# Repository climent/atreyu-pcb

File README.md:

# atreyu-pcb
## Intro 
This project is the evolution of the [Atreyu Keyboard](http://github.com/climent/atreyu) project, an ergonomic keyboard that was handwired only.

I aimed to increase the appeal of this board by designing a PCB for it, and through the next months learned how to design one.

The first release of the keyboard (v0.1) is ready, and looks like this:

## Want to collaborate?

You can execute

```git clone --recurse-submodules https://github.com/climent/atryeu-pcb.git```

and send me a pull request.

have fun!

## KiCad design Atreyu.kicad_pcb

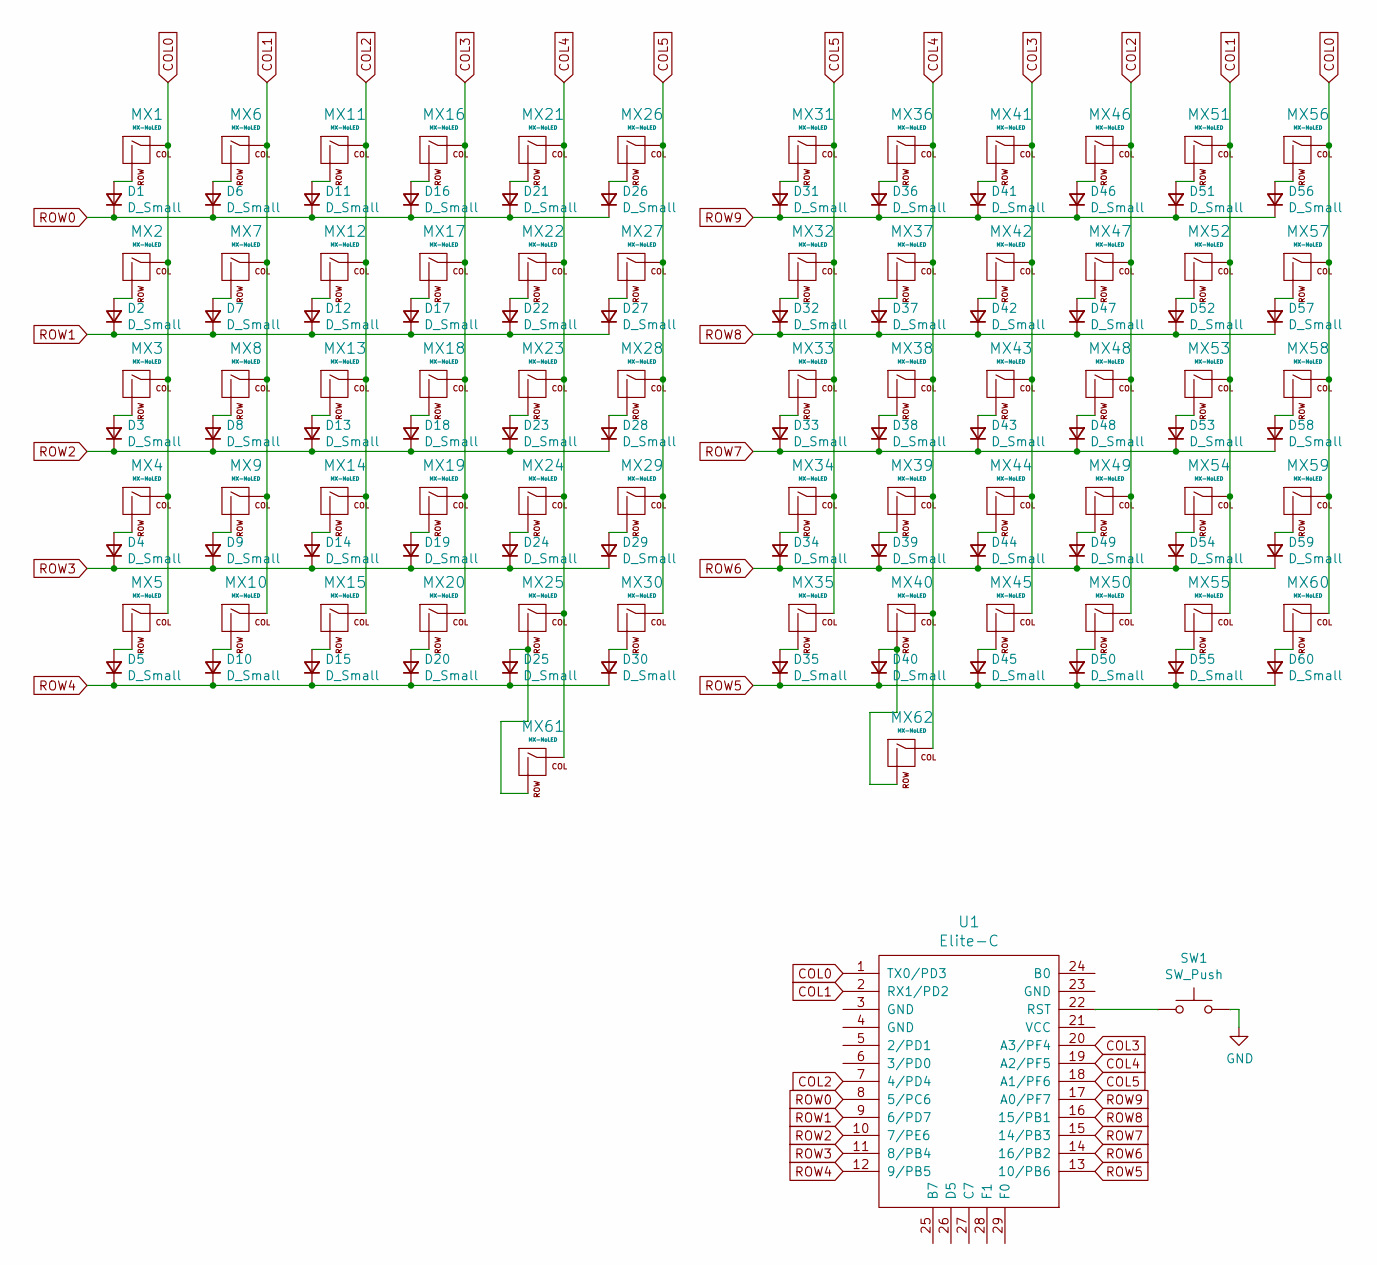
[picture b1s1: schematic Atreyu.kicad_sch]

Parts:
D1, D2, D3, D4, D5, D6, D7, D8, D9, D10, D11, D12, D13, D14, D15, D16, D17, D18, D19, D20, D21, D22, D23, D24, D25, D26, D27, D28, D29, D30, D31, D32, D33, D34, D35, D36, D37, D38, D39, D40, D41, D42, D43, D44, D45, D46, D47, D48, D49, D50, D51, D52, D53, D54, D55, D56, D57, D58, D59, D60: D_Small; D3_hybrid_common_hole
MX1, MX2, MX3, MX4, MX5, MX6, MX7, MX8, MX9, MX10, MX11, MX12, MX13, MX14, MX15, MX16, MX17, MX18, MX19, MX20, MX21, MX22, MX23, MX24, MX25, MX26, MX27, MX28, MX29, MX30, MX31, MX32, MX33, MX34, MX35, MX36, MX37, MX38, MX39, MX40, MX41, MX42, MX43, MX44, MX45, MX46, MX47, MX48, MX49, MX50, MX51, MX52, MX53, MX54, MX55, MX56, MX57, MX58, MX59, MX60, MX61, MX62: MX-NoLED; CherryMX_Hotswap
SW1: SW_Push; ResetSW_1side
U1: Elite-C

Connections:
COL0: MX1.1 (COL), MX2.1 (COL), MX3.1 (COL), MX4.1 (COL), MX5.1 (COL), MX56.1 (COL), MX57.1 (COL), MX58.1 (COL), MX59.1 (COL), MX60.1 (COL), U1.1 (TX0/PD3)
COL1: MX6.1 (COL), MX7.1 (COL), MX8.1 (COL), MX9.1 (COL), MX10.1 (COL), MX51.1 (COL), MX52.1 (COL), MX53.1 (COL), MX54.1 (COL), MX55.1 (COL), U1.2 (RX1/PD2)
COL2: MX11.1 (COL), MX12.1 (COL), MX13.1 (COL), MX14.1 (COL), MX15.1 (COL), MX46.1 (COL), MX47.1 (COL), MX48.1 (COL), MX49.1 (COL), MX50.1 (COL), U1.7 (4/PD4)
COL3: MX16.1 (COL), MX17.1 (COL), MX18.1 (COL), MX19.1 (COL), MX20.1 (COL), MX41.1 (COL), MX42.1 (COL), MX43.1 (COL), MX44.1 (COL), MX45.1 (COL), U1.20 (A3/PF4)
COL4: MX21.1 (COL), MX22.1 (COL), MX23.1 (COL), MX24.1 (COL), MX25.1 (COL), MX36.1 (COL), MX37.1 (COL), MX38.1 (COL), MX39.1 (COL), MX40.1 (COL), MX61.1 (COL), MX62.1 (COL), U1.19 (A2/PF5)
COL5: MX26.1 (COL), MX27.1 (COL), MX28.1 (COL), MX29.1 (COL), MX30.1 (COL), MX31.1 (COL), MX32.1 (COL), MX33.1 (COL), MX34.1 (COL), MX35.1 (COL), U1.18 (A1/PF6)
GND: SW1.2
unnamed: D1.2 (A), MX1.2 (ROW)
unnamed: D2.2 (A), MX2.2 (ROW)
unnamed: D3.2 (A), MX3.2 (ROW)
unnamed: D4.2 (A), MX4.2 (ROW)
unnamed: D5.2 (A), MX5.2 (ROW)
unnamed: D6.2 (A), MX6.2 (ROW)
unnamed: D7.2 (A), MX7.2 (ROW)
unnamed: D8.2 (A), MX8.2 (ROW)
unnamed: D9.2 (A), MX9.2 (ROW)
unnamed: D10.2 (A), MX10.2 (ROW)
unnamed: D11.2 (A), MX11.2 (ROW)
unnamed: D12.2 (A), MX12.2 (ROW)
unnamed: D13.2 (A), MX13.2 (ROW)
unnamed: D14.2 (A), MX14.2 (ROW)
unnamed: D15.2 (A), MX15.2 (ROW)
unnamed: D16.2 (A), MX16.2 (ROW)
unnamed: D17.2 (A), MX17.2 (ROW)
unnamed: D18.2 (A), MX18.2 (ROW)
unnamed: D19.2 (A), MX19.2 (ROW)
unnamed: D20.2 (A), MX20.2 (ROW)
unnamed: D21.2 (A), MX21.2 (ROW)
unnamed: D22.2 (A), MX22.2 (ROW)
unnamed: D23.2 (A), MX23.2 (ROW)
unnamed: D24.2 (A), MX24.2 (ROW)
unnamed: D25.2 (A), MX25.2 (ROW), MX61.2 (ROW)
unnamed: D26.2 (A), MX26.2 (ROW)
unnamed: D27.2 (A), MX27.2 (ROW)
unnamed: D28.2 (A), MX28.2 (ROW)
unnamed: D29.2 (A), MX29.2 (ROW)
unnamed: D30.2 (A), MX30.2 (ROW)
unnamed: D31.2 (A), MX31.2 (ROW)
unnamed: D32.2 (A), MX32.2 (ROW)
unnamed: D33.2 (A), MX33.2 (ROW)
unnamed: D34.2 (A), MX34.2 (ROW)
unnamed: D35.2 (A), MX35.2 (ROW)
unnamed: D36.2 (A), MX36.2 (ROW)
unnamed: D37.2 (A), MX37.2 (ROW)
unnamed: D38.2 (A), MX38.2 (ROW)
unnamed: D39.2 (A), MX39.2 (ROW)
unnamed: D40.2 (A), MX40.2 (ROW), MX62.2 (ROW)
unnamed: D41.2 (A), MX41.2 (ROW)
unnamed: D42.2 (A), MX42.2 (ROW)
unnamed: D43.2 (A), MX43.2 (ROW)
unnamed: D44.2 (A), MX44.2 (ROW)
unnamed: D45.2 (A), MX45.2 (ROW)
unnamed: D46.2 (A), MX46.2 (ROW)
unnamed: D47.2 (A), MX47.2 (ROW)
unnamed: D48.2 (A), MX48.2 (ROW)
unnamed: D49.2 (A), MX49.2 (ROW)
unnamed: D50.2 (A), MX50.2 (ROW)
unnamed: D51.2 (A), MX51.2 (ROW)
unnamed: D52.2 (A), MX52.2 (ROW)
unnamed: D53.2 (A), MX53.2 (ROW)
unnamed: D54.2 (A), MX54.2 (ROW)
unnamed: D55.2 (A), MX55.2 (ROW)
unnamed: D56.2 (A), MX56.2 (ROW)
unnamed: D57.2 (A), MX57.2 (ROW)
unnamed: D58.2 (A), MX58.2 (ROW)
unnamed: D59.2 (A), MX59.2 (ROW)
unnamed: D60.2 (A), MX60.2 (ROW)
unnamed: SW1.1, U1.22 (RST)
ROW0: D1.1 (K), D6.1 (K), D11.1 (K), D16.1 (K), D21.1 (K), D26.1 (K), U1.8 (5/PC6)
ROW1: D2.1 (K), D7.1 (K), D12.1 (K), D17.1 (K), D22.1 (K), D27.1 (K), U1.9 (6/PD7)
ROW2: D3.1 (K), D8.1 (K), D13.1 (K), D18.1 (K), D23.1 (K), D28.1 (K), U1.10 (7/PE6)
ROW3: D4.1 (K), D9.1 (K), D14.1 (K), D19.1 (K), D24.1 (K), D29.1 (K), U1.11 (8/PB4)
ROW4: D5.1 (K), D10.1 (K), D15.1 (K), D20.1 (K), D25.1 (K), D30.1 (K), U1.12 (9/PB5)
ROW5: D35.1 (K), D40.1 (K), D45.1 (K), D50.1 (K), D55.1 (K), D60.1 (K), U1.13 (10/PB6)
ROW6: D34.1 (K), D39.1 (K), D44.1 (K), D49.1 (K), D54.1 (K), D59.1 (K), U1.14 (16/PB2)
ROW7: D33.1 (K), D38.1 (K), D43.1 (K), D48.1 (K), D53.1 (K), D58.1 (K), U1.15 (14/PB3)
ROW8: D32.1 (K), D37.1 (K), D42.1 (K), D47.1 (K), D52.1 (K), D57.1 (K), U1.16 (15/PB1)
ROW9: D31.1 (K), D36.1 (K), D41.1 (K), D46.1 (K), D51.1 (K), D56.1 (K), U1.17 (A0/PF7)

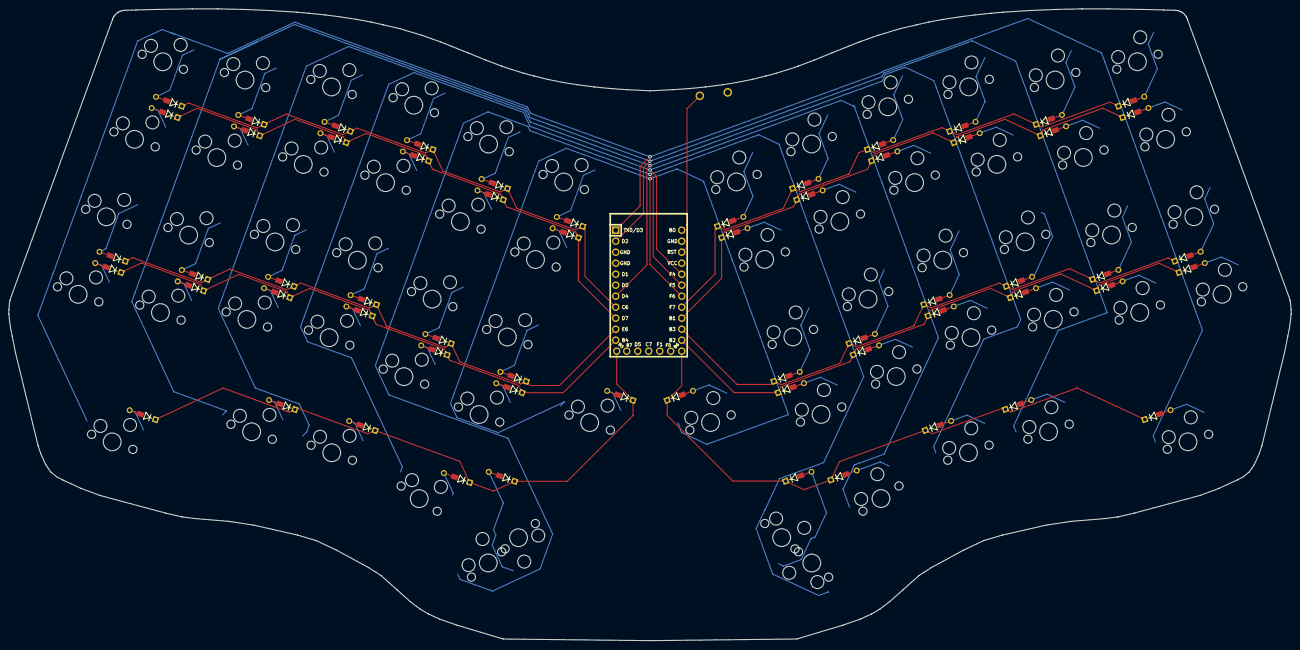
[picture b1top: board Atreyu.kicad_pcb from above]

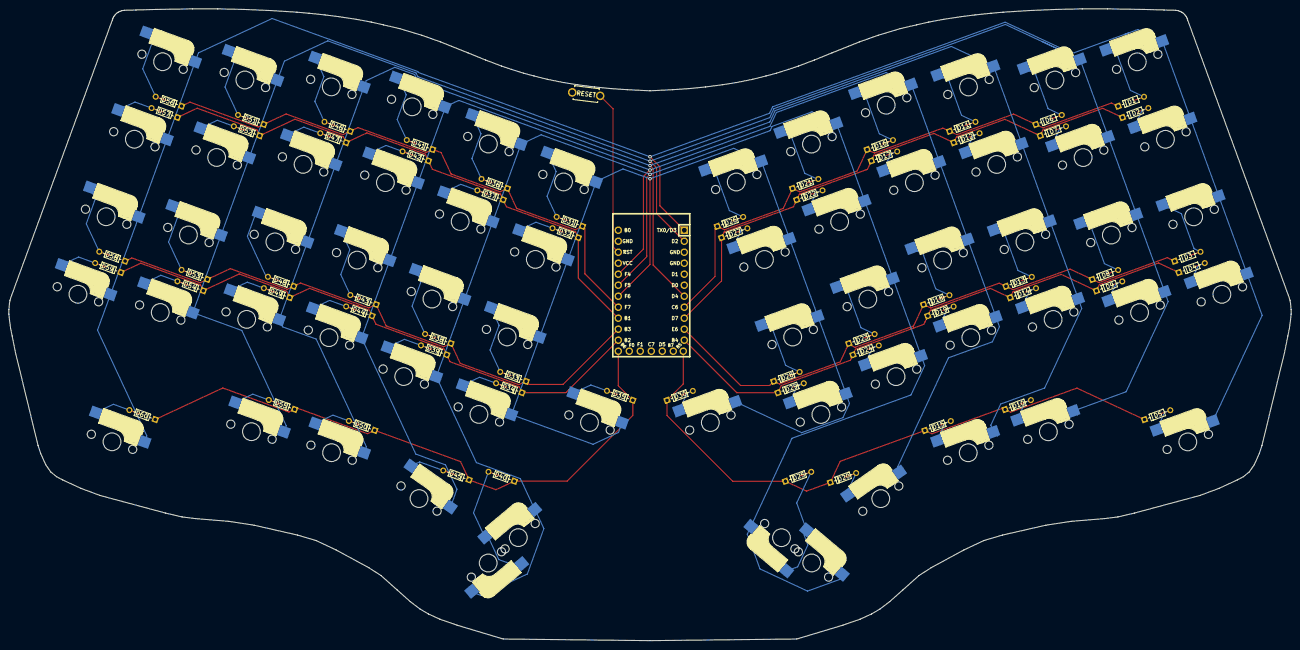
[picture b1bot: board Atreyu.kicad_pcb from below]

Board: 2 copper layers, 296.2 x 145.9 mm, 124 parts (61 on the bottom side), 77 nets.

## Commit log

2021-06-13 Add submodules.
2021-06-13 Added keebio submodule and configured libraries for schem and footprint.
2021-06-13 Schematic completed.
2021-06-14 PCB initial commit.
2021-06-17 Checkpoint commit.
2021-06-22 Last update.
2021-06-23 Added new module.
2021-06-26 Added new symbols/footprints library.
2021-06-26 Readme file with clone instructions (with submodules).
2021-06-26 Complete URL.
2021-12-30 Tracks routed and sides aligned with the edge cuts layer.
2021-12-31 Created Atreyu local footprint library.
2022-01-01 Completed v0.1.
2022-01-01 Added the first picture.
2022-01-01 Fix image name.
2022-01-01 Moved reset button to the right and added SVG file with contour.
